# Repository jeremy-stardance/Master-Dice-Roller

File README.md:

# Master-Dice-Roller
Week 5 of Hack Club Half-Life

# PCB

My circuit should allow me to display up to 20 lights at once to communicate a result. I have avoided binary to make the results easier and more convenient to read. I was going to use binary inspired LED organisation and put 1, 2, 4, 8, and 16 LEDs on a single pin to allow for more buttons, but that could blow the Arduino Pro Micro, so I am limited to 4 buttons, which i will probably assign d4, d6, d8, d20, and just change when necessary.#

# Schematic

Here is how the PCB will work.

# Bill Of Materials

| Component | Quantity | Cost ($) |
|---|---:|---:|
| 220 Ohm Resistors | 1 pack of 50 | 1.43 |
| Buttons | 1 pack | 6.00|
| Breadboard Kit | 1 | 12.42 |

The rest (LEDs, Pro Micro, Breadboard) I can reuse from previous projects to minimize costs.

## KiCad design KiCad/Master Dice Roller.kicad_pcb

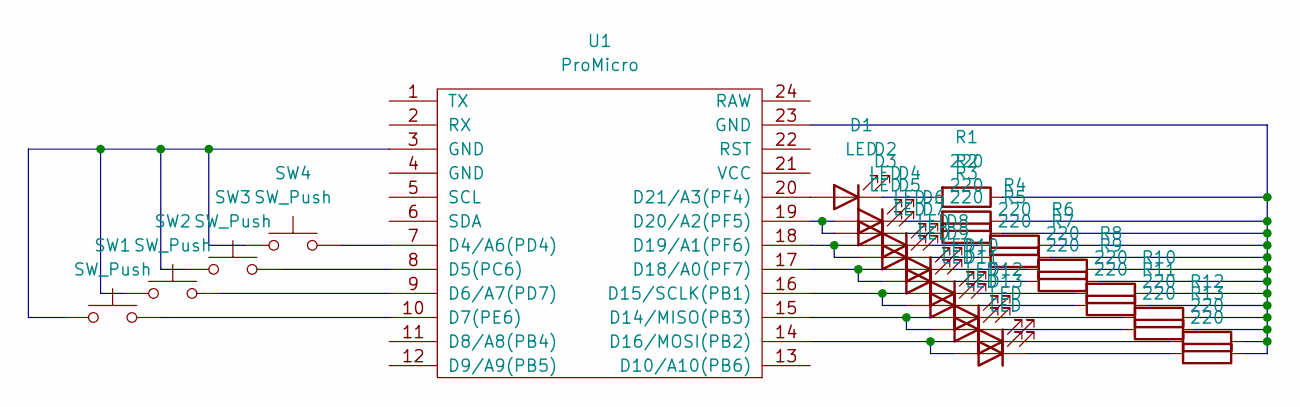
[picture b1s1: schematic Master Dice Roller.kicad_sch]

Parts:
D1, D2, D3, D4, D5, D6, D7, D8, D9, D10, D11, D12, D13: LED; LED_D5.0mm
R1, R2, R3, R4, R5, R6, R7, R8, R9, R10, R11, R12, R13: 220; R_0201_0603Metric
SW1, SW2, SW3, SW4: SW_Push; SW_Cherry_MX_1.00u_PCB
U1: ProMicro

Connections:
unnamed: D1.2 (A), U1.20 (D21/A3(PF4))
unnamed: D1.1 (K), R1.2
unnamed: D2.2 (A), D3.2 (A), U1.19 (D20/A2(PF5))
unnamed: D2.1 (K), R2.2
unnamed: D3.1 (K), R3.2
unnamed: D4.2 (A), D5.2 (A), U1.18 (D19/A1(PF6))
unnamed: D4.1 (K), R4.2
unnamed: D5.1 (K), R5.2
unnamed: D6.2 (A), D7.2 (A), U1.17 (D18/A0(PF7))
unnamed: D6.1 (K), R6.2
unnamed: D7.1 (K), R7.2
unnamed: D8.2 (A), D9.2 (A), U1.16 (D15/SCLK(PB1))
unnamed: D8.1 (K), R8.2
unnamed: D9.1 (K), R9.2
unnamed: D10.2 (A), D11.2 (A), U1.15 (D14/MISO(PB3))
unnamed: D10.1 (K), R10.2
unnamed: D11.1 (K), R11.2
unnamed: D12.2 (A), D13.2 (A), U1.14 (D16/MOSI(PB2))
unnamed: D12.1 (K), R12.2
unnamed: D13.1 (K), R13.2
unnamed: R1.1, R2.1, R3.1, R4.1, R5.1, R6.1, R7.1, R8.1, R9.1, R10.1, R11.1, R12.1, R13.1, U1.23 (GND)
unnamed: SW1.1, SW2.1, SW3.1, SW4.1, U1.3 (GND)
unnamed: SW4.2, U1.7 (D4/A6(PD4))
unnamed: SW3.2, U1.8 (D5(PC6))
unnamed: SW2.2, U1.9 (D6/A7(PD7))
unnamed: SW1.2, U1.10 (D7(PE6))

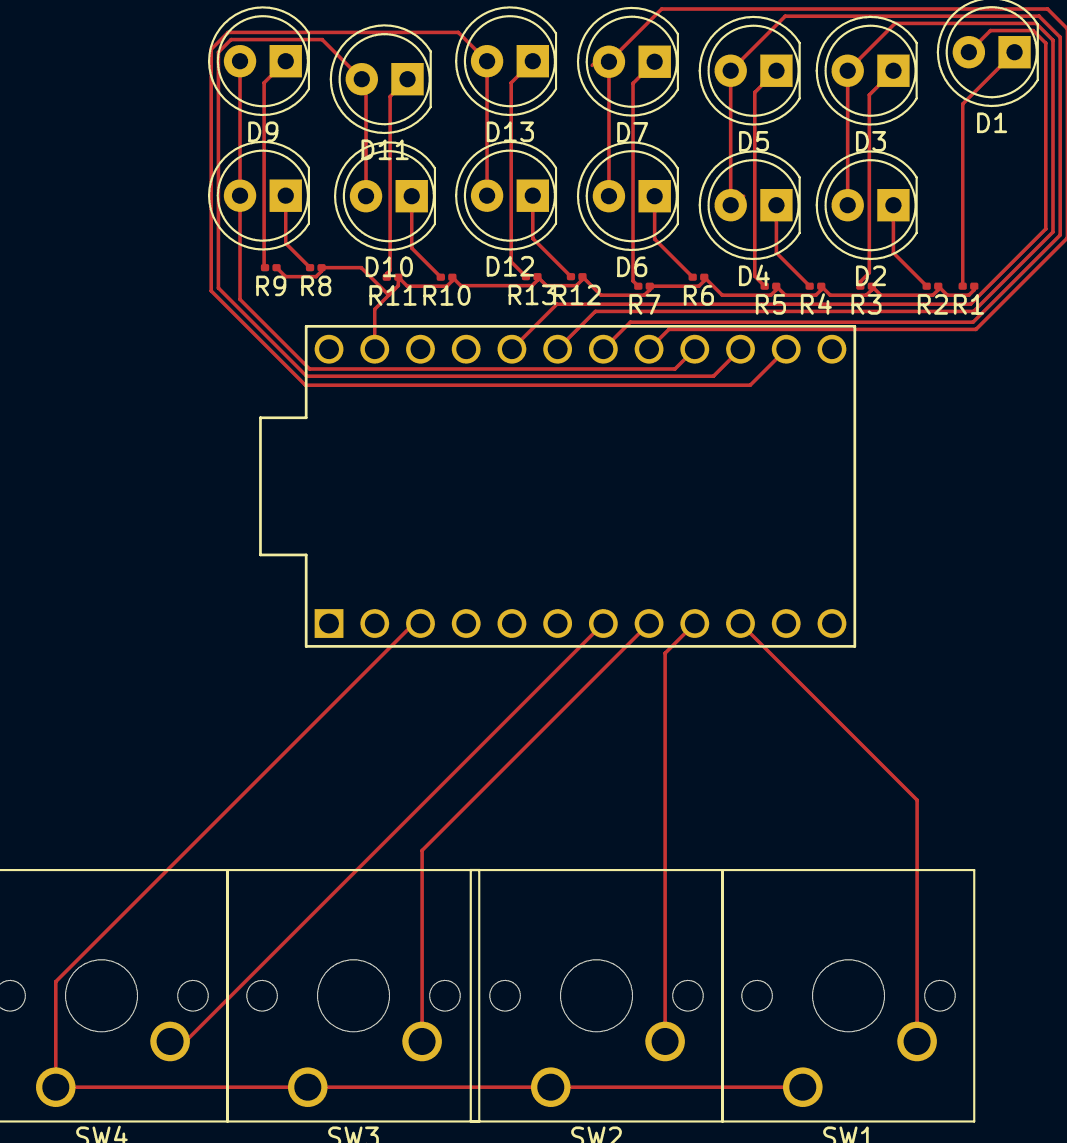
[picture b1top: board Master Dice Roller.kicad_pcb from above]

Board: 2 copper layers, 31 parts (0 on the bottom side), 26 nets.
